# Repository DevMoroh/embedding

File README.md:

# Мостовий підсилювач (KiCad)

Схема й двошарова друкована плата підсилювача сигналу з резистивного моста: міст → інструментальний підсилювач на двох ОП → диференційний каскад. Проєкт для KiCad 10.

## Як працює схема

- **Міст** R10/R11+R12+R14 (ліве плече) і R13/R9+R15 (праве плече) живиться від 3,3 В. R11 імітує датчик, R15 («Нуль») балансує міст. Сигнали плечей — `a1` і `a2`.
- **RC-фільтри** R17/C1 і R16/C2 (1 кОм, 0,1 мкФ, ≈1,6 кГц) зрізають наводки на входах.
- **Вхідний каскад** U1A/U1B — класичний інструментальний підсилювач: R22 = R24 = 10 кОм, підсилення задає ланцюжок R25 + R23 («Кп») між інвертувальними входами: `1 + 2·10k / (R25 + R23)`, від 9 до ≈14,3.
- **Диференційний каскад** U1C (R18 = R20 = 1 кОм, R19 = R21 = 10 кОм) віднімає `out1 − out2` з підсиленням 10 і дає однополярний вихід `out3`.
- Загалом `Vout = (a1 − a2) · (1 + 2·10k / (R25 + R23)) · 10`, тобто від 90 до ≈143.

Операційний підсилювач — **MCP6004** (чотири ОП в одному корпусі DIP-14, rail-to-rail вхід і вихід, живлення 1,8–6 В), тож усе працює від 3,3 В. Четвертий ОП (U1D) не використовується і ввімкнений повторювачем із входом на GND, щоб не збуджувався.

## Плата

- 80 × 54 мм, 2 шари, усі компоненти вивідні (THT), 4 отвори M3 по кутах.
- Сигнал іде зліва направо, як на схемі: міст → фільтри → U1 → диференційний каскад → роз'єм J1.
- Доріжки майже всі на верхньому шарі (сигнальні 0,3 мм, живлення 0,5 мм). Нижній шар — суцільний полігон GND, на верхньому полігон GND заповнює вільне місце. Перехідних отворів — 3.
- C3 (0,1 мкФ) стоїть біля U1, C4 (10 мкФ) — біля роз'єму живлення.
- Підстроювальні резистори Bourns 3296W: R11 (датчик), R15 («Нуль»), R23 («Кп»).

**J1** (гребінка 2,54 мм): 1 — +3V3, 2 — OUT (вихід `out3`, наприклад на АЦП ESP32/STM32), 3 — GND.

## Перевірка

- ERC схеми: 0 помилок і попереджень.
- DRC плати зі звіркою зі схемою: 0 порушень, 0 непідключених виводів, 0 розбіжностей.
- Netlist схеми автоматично звіряється зі схемою зі скріну уроку (`scripts/check_net.py`).

## Структура

- `Amplifier.kicad_pro`, `Amplifier.kicad_sch`, `Amplifier.kicad_pcb` — проєкт KiCad
- `docs/` — зображення схеми й плати, PDF схеми
- `scripts/` — генерація проєкту:
  - `gen_sch.py` — схема (розміщення символів і дротів)
  - `place.py` — розміщення компонентів на платі
  - `router.py` — трасувальник доріжок (A* на сітці 0,3175 мм, 2 шари, перевірка зазорів)
  - `gen_pcb.py` — плата через Python API KiCad (`pcbnew`)
  - `build.sh` — повна збірка з ERC/DRC (macOS, KiCad 10, для PNG потрібен Google Chrome)

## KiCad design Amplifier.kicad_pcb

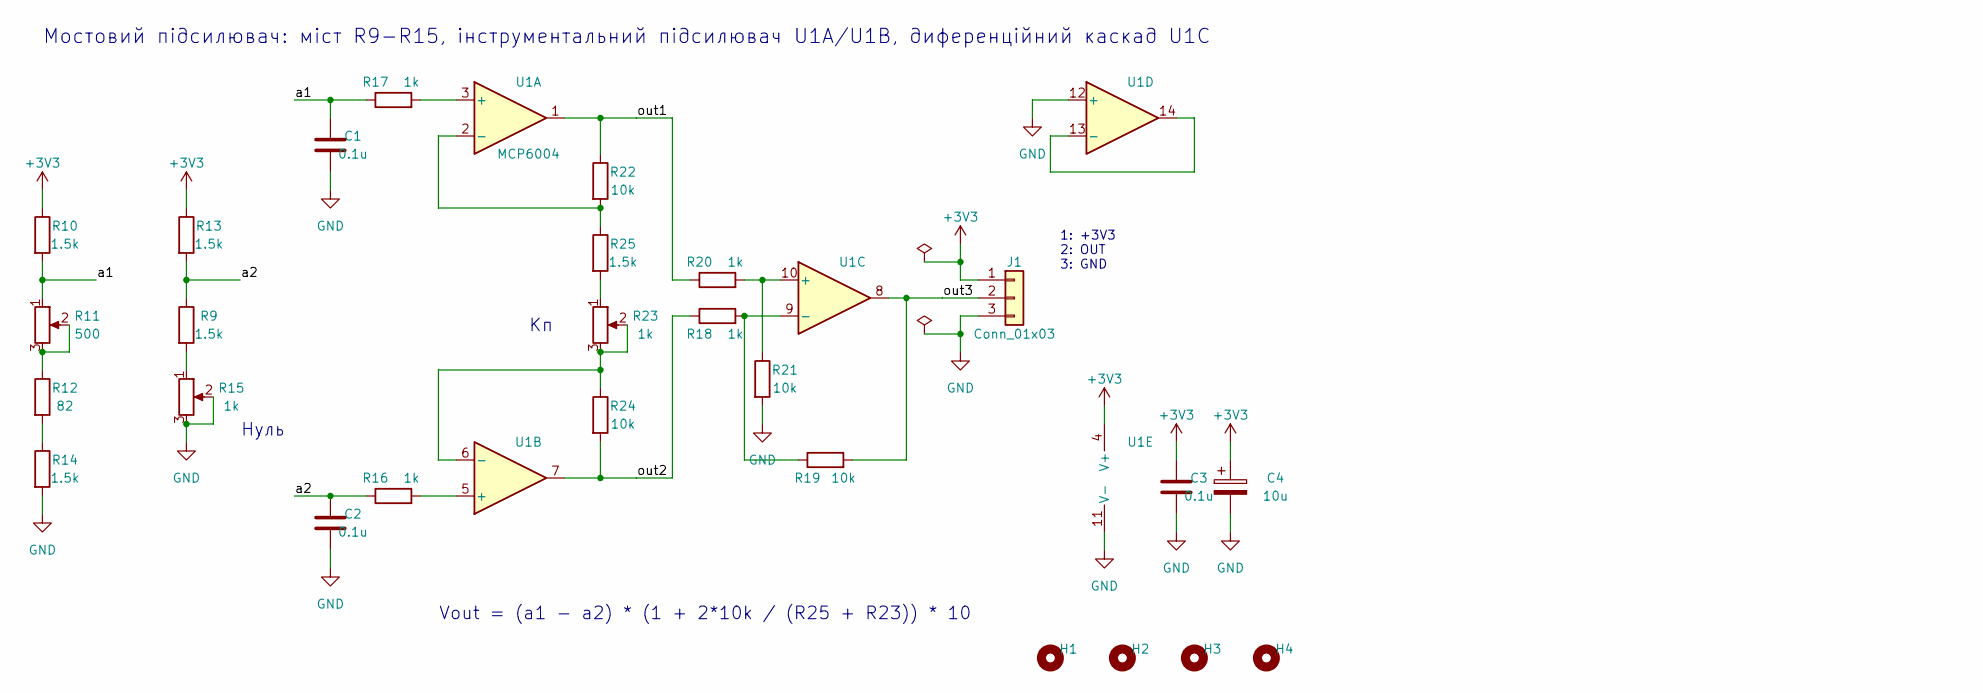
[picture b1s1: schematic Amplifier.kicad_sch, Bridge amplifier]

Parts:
C1, C2, C3: 0.1u; C_Disc_D5.0mm_W2.5mm_P5.00mm
C4: 10u; CP_Radial_D5.0mm_P2.00mm
H1, H2, H3, H4: MountingHole; MountingHole_3.2mm_M3
J1: Conn_01x03; PinHeader_1x03_P2.54mm_Vertical
R9, R10, R13, R14, R25: 1.5k; R_Axial_DIN0207_L6.3mm_D2.5mm_P7.62mm_Horizontal
R11: 500; Potentiometer_Bourns_3296W_Vertical
R12: 82; R_Axial_DIN0207_L6.3mm_D2.5mm_P7.62mm_Horizontal
R15, R23: 1k; Potentiometer_Bourns_3296W_Vertical
R16, R17, R18, R20: 1k; R_Axial_DIN0207_L6.3mm_D2.5mm_P7.62mm_Horizontal
R19, R21, R22, R24: 10k; R_Axial_DIN0207_L6.3mm_D2.5mm_P7.62mm_Horizontal
U1: MCP6004; DIP-14_W7.62mm

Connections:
+3V3: C3.1, C4.1, J1.1, R10.1, R13.1, U1.4 (V+)
/a1: C1.1, R10.2, R11.1, R17.1
/a2: C2.1, R9.1, R13.2, R16.1
/out1: R20.1, R22.1, U1.1
/out2: R18.1, R24.2, U1.7
/out3: J1.2, R19.2, U1.8
GND: C1.2, C2.2, C3.2, C4.2, J1.3, R14.2, R15.2, R15.3, R21.2, U1.11 (V-), U1.12 (+)
unnamed: R11.2, R11.3, R12.1
unnamed: R12.2, R14.1
unnamed: R9.2, R15.1
unnamed: R23.1, R25.2
unnamed: R17.2, U1.3 (+)
unnamed: R22.2, R25.1, U1.2 (-)
unnamed: R16.2, U1.5 (+)
unnamed: R23.2, R23.3, R24.1, U1.6 (-)
unnamed: R20.2, R21.1, U1.10 (+)
unnamed: R18.2, R19.1, U1.9 (-)
unnamed: U1.13 (-), U1.14

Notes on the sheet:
Нуль
1: +3V3 2: OUT 3: GND
Мостовий підсилювач: міст R9-R15, інструментальний підсилювач U1A/U1B, диференційний каскад U1C
Vout = (a1 - a2) * (1 + 2*10k / (R25 + R23)) * 10

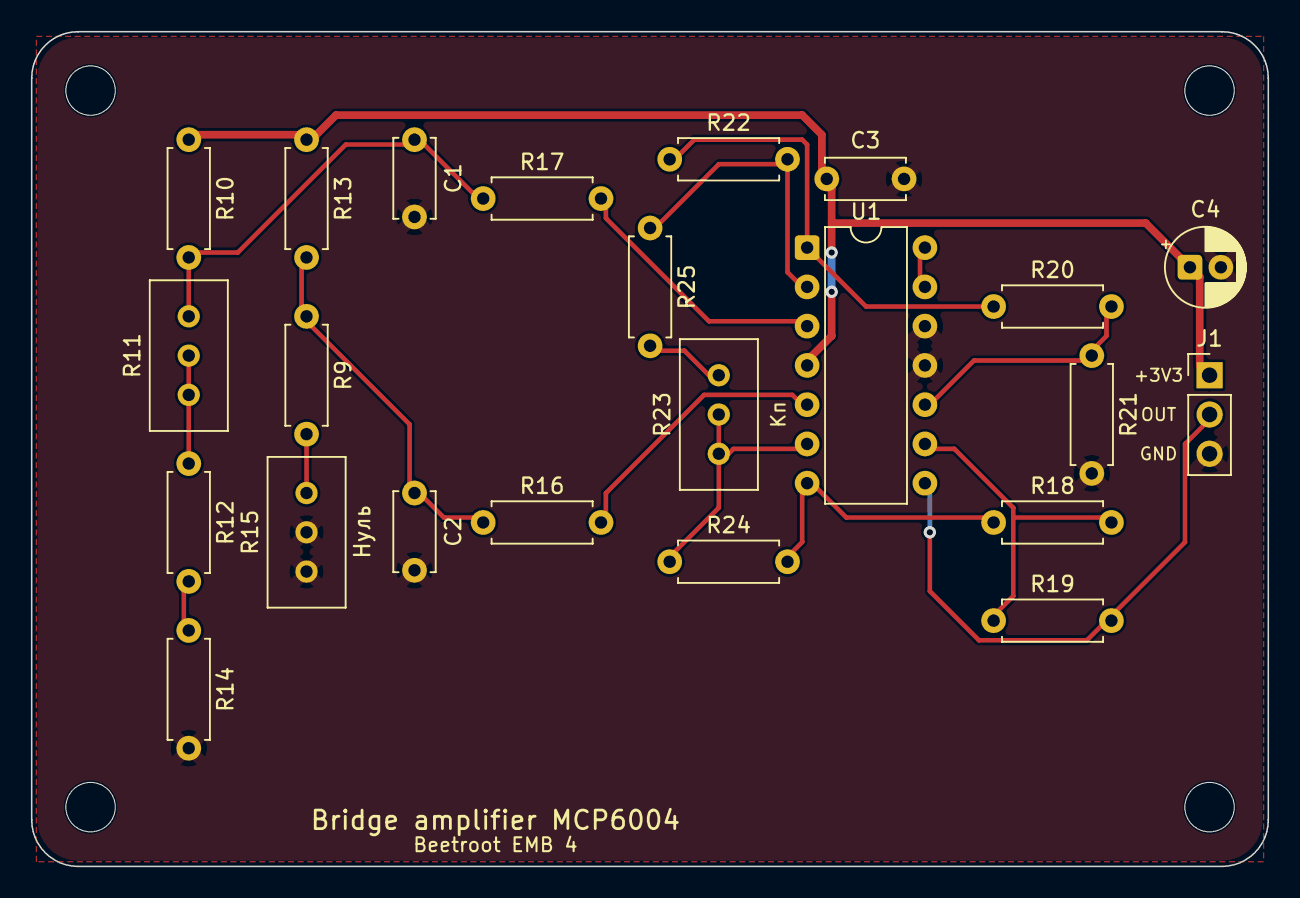
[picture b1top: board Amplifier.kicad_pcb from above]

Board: 2 copper layers, 80.0 x 54.0 mm, 27 parts (0 on the bottom side), 18 nets.

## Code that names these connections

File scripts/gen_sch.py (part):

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r18_in, r18_out = sorted([r18['1'], r18['2']])
r19_in, r19_out = sorted([r19['1'], r19['2']])
wire((39, 10), (43, 10), (43, 19), r20_in)
label('out1', 41, 10)
wire((39, 30), (43, 30), (43, 21), r18_in)
label('out2', 41, 30)
wire(r20_out, (48, 19), uc['10'])
wire((48, 19), r21['1'])
wire(r21['2'], (48, 27))
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wire(r18_out, (47, 29), r19_in)
wire(uc['8'], (56, 20), (60, 20))
wire(r19_out, (56, 29), (56, 20))
label('out3', 58, 20)

# Роз'єм: 1 = +3V3, 2 = OUT3, 3 = GND
j1 = place('J', 'J1', 'Conn_01x03', 62, 20, desc='1: +3V3, 2: OUT3, 3: GND')
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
